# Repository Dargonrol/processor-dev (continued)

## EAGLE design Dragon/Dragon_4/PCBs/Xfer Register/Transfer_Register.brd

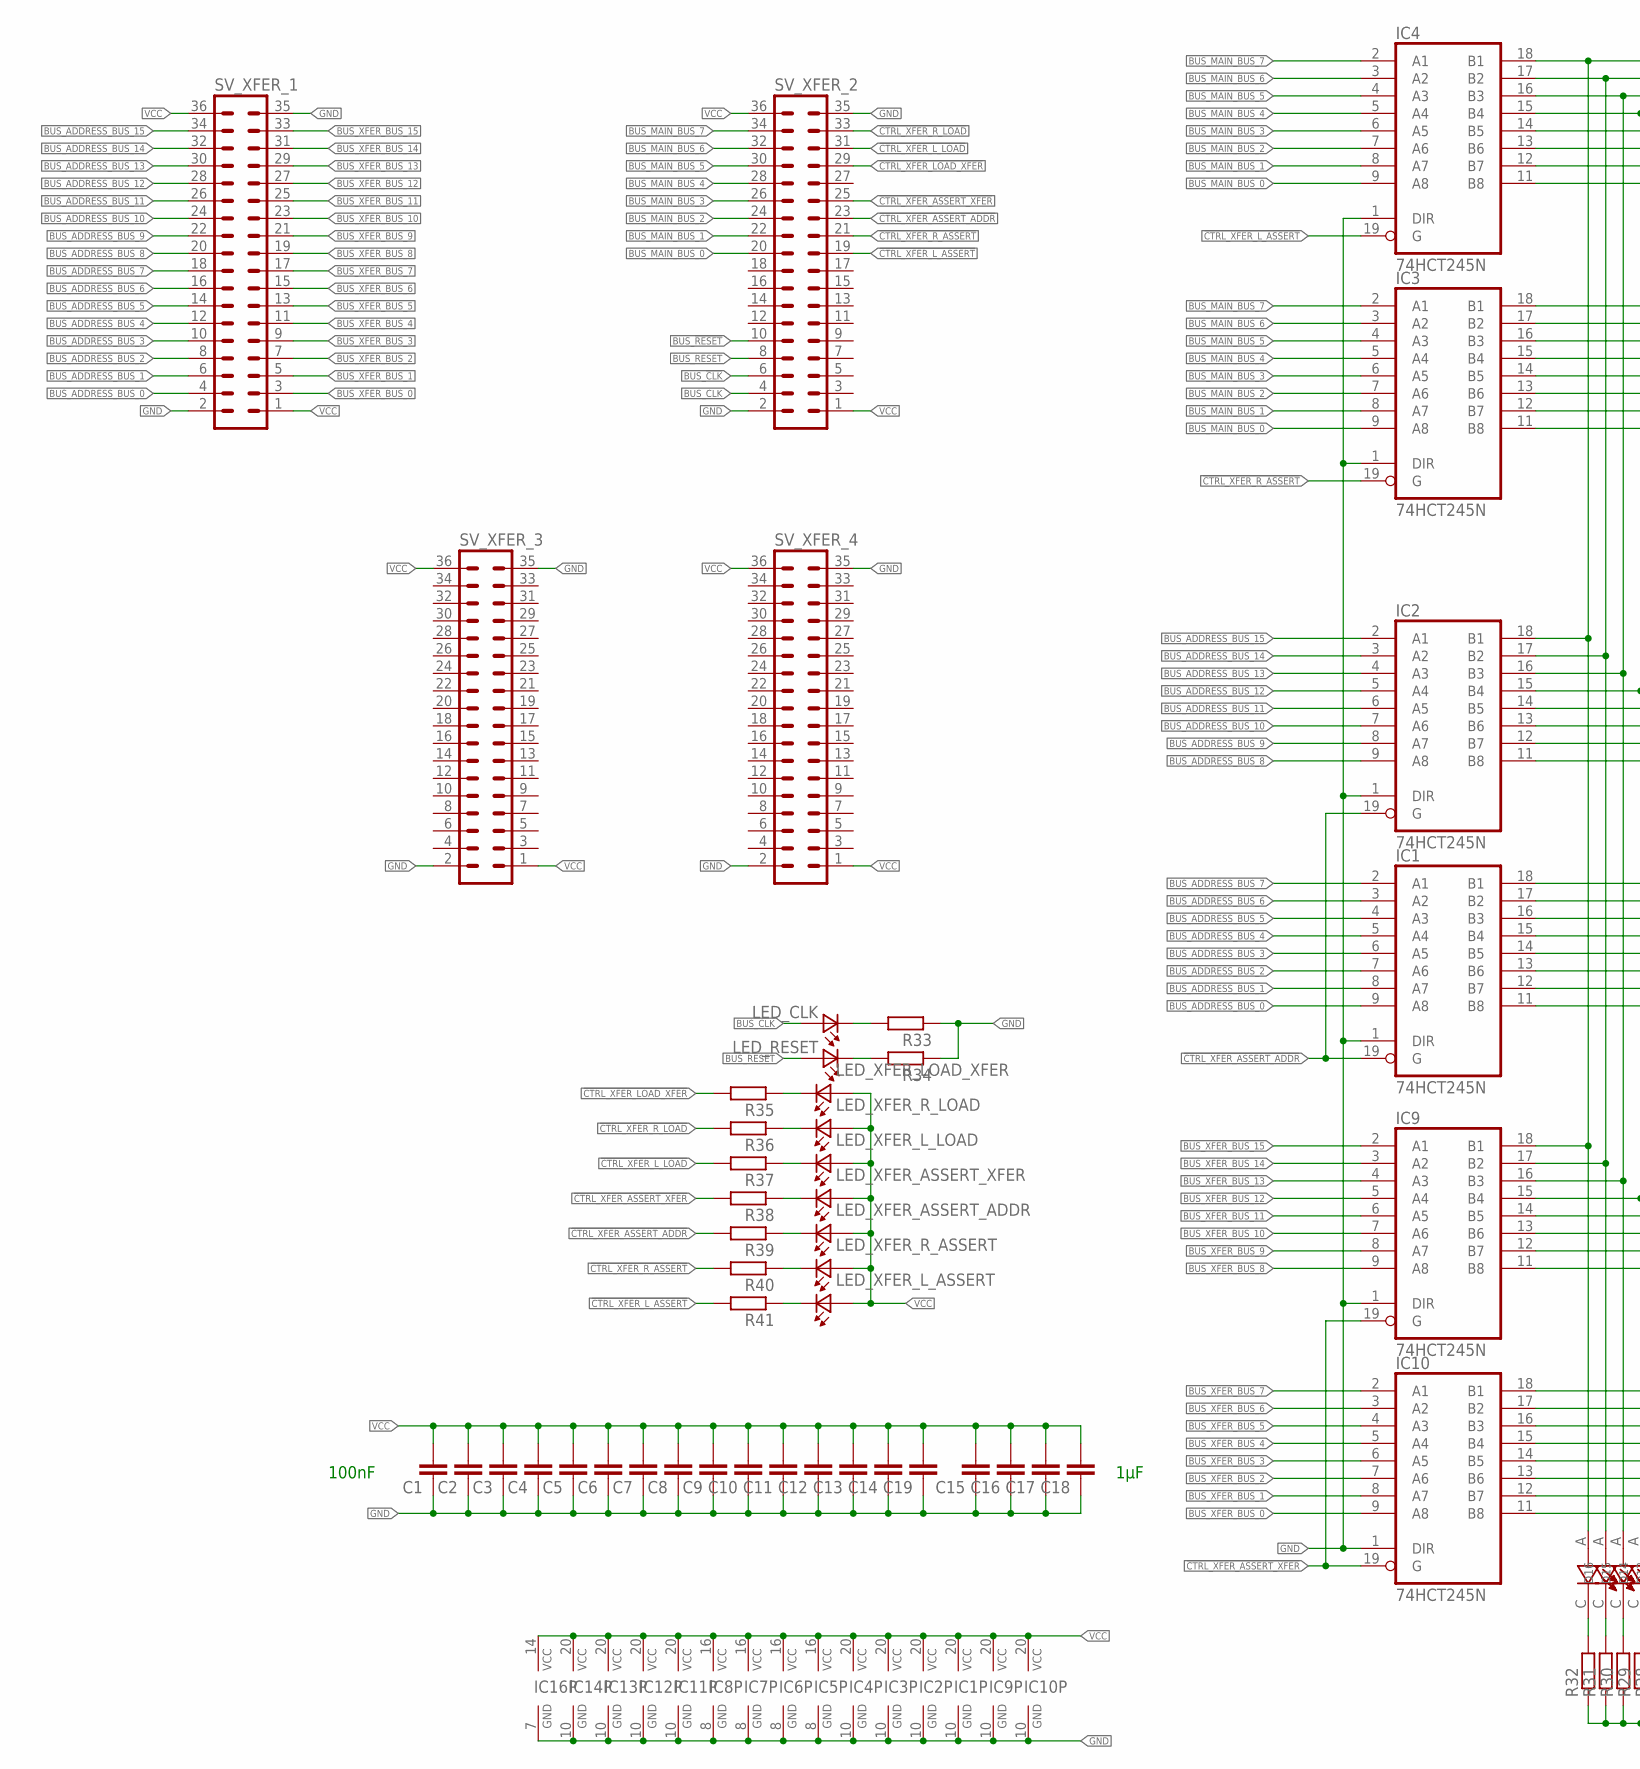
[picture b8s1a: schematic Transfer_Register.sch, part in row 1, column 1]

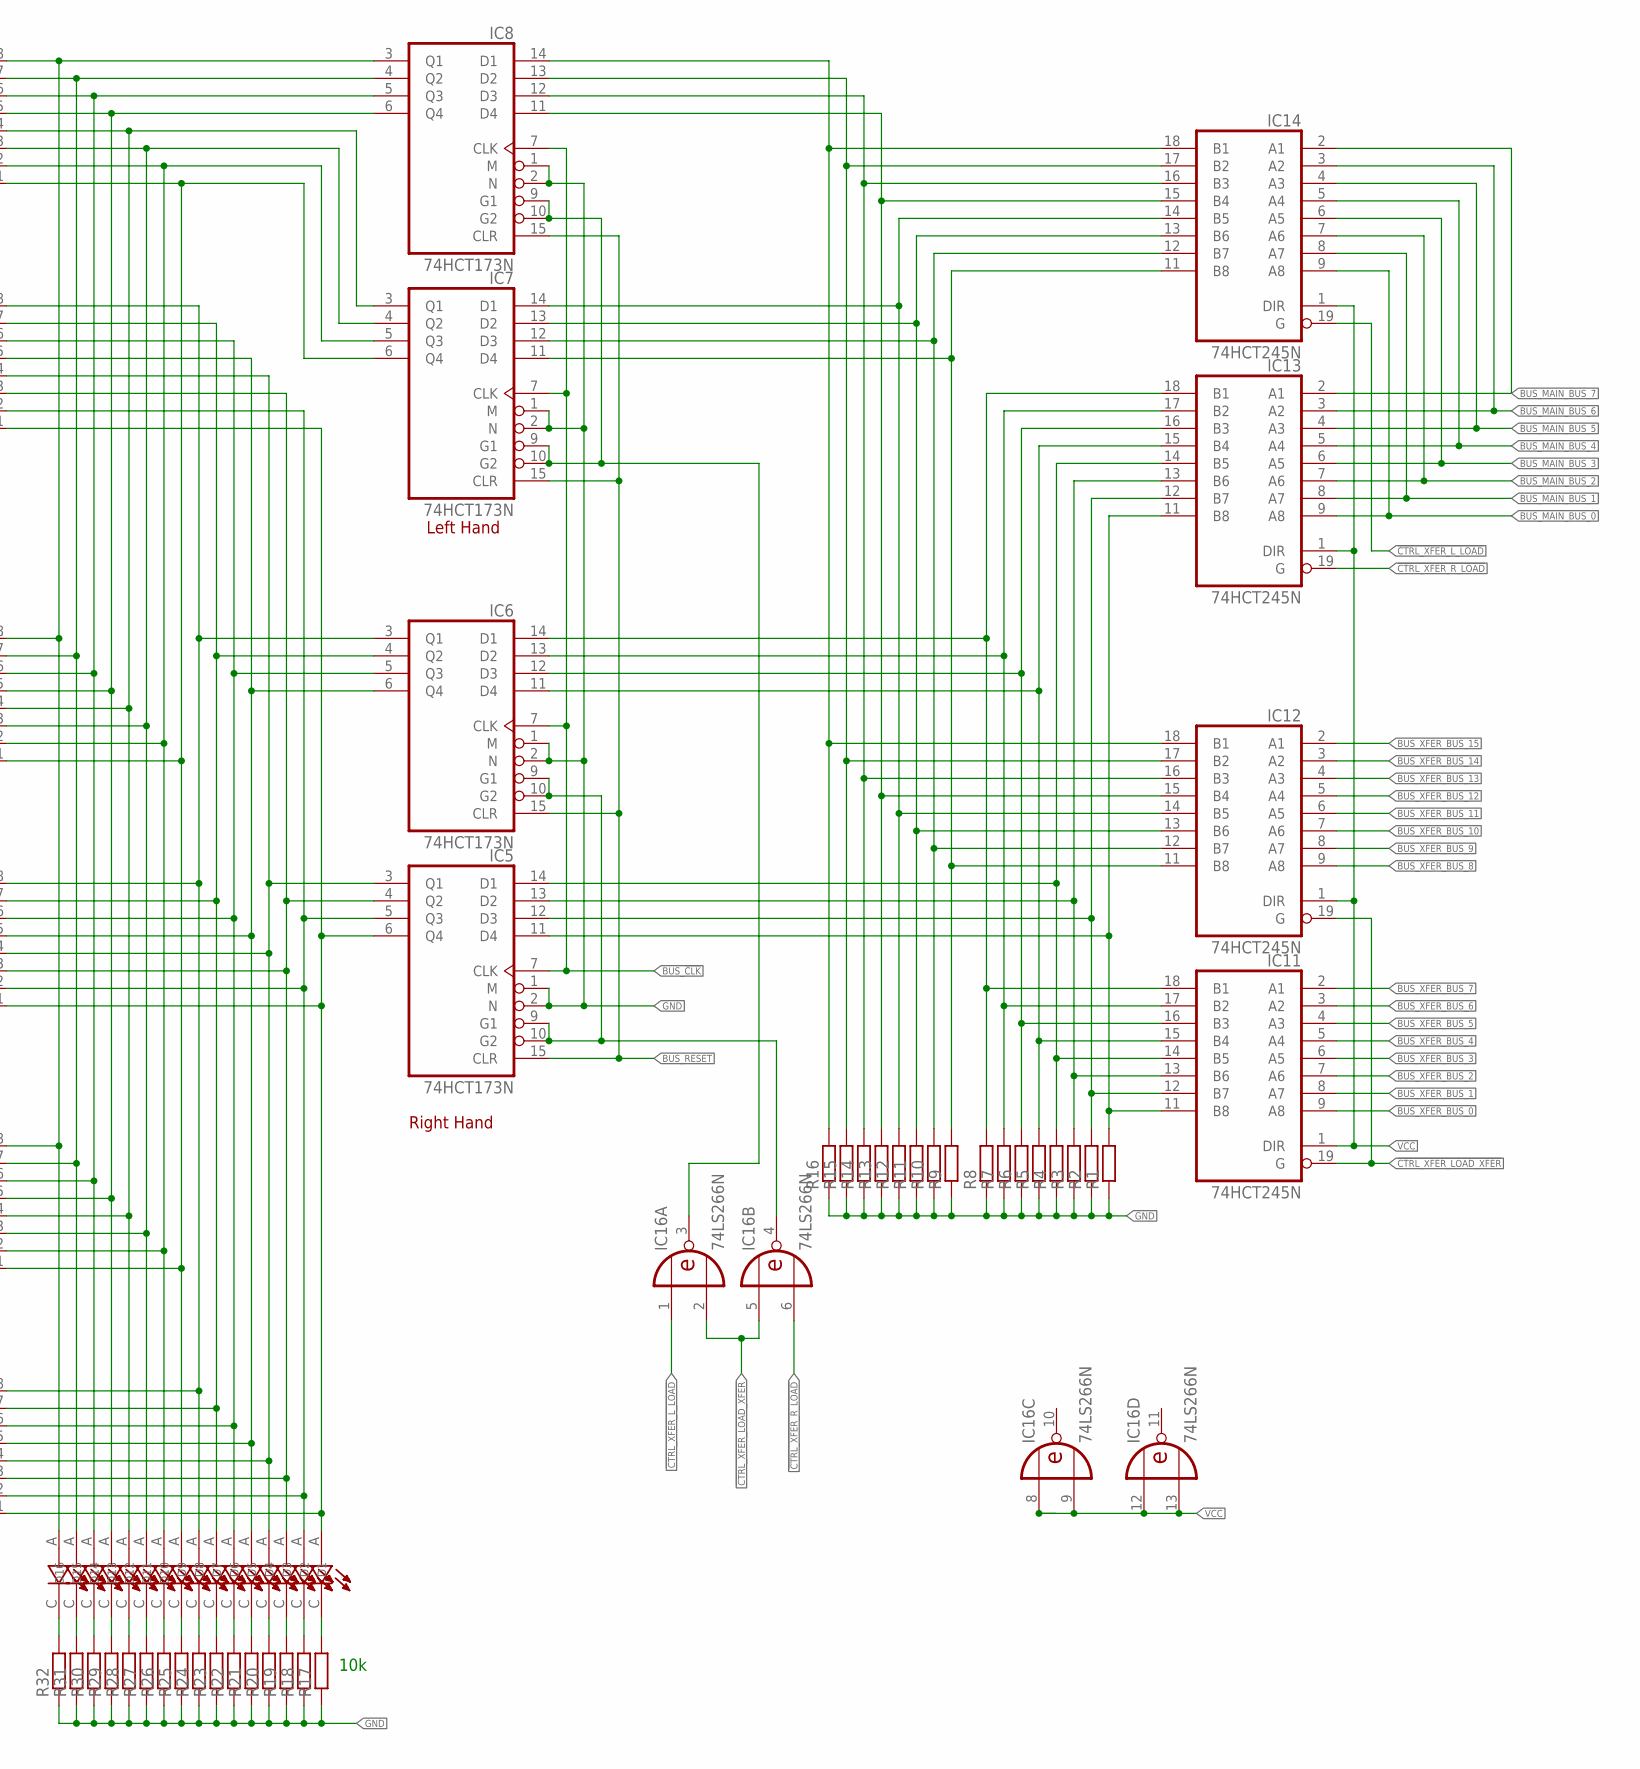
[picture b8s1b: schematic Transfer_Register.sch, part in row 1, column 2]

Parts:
C1, C2, C3, C4, C5, C6, C7, C8, C9, C10, C11, C12, C13, C14, C15, C16, C17, C18, C19: C-EUC0805; C0805
D1, D2, D3, D4, D5, D6, D7, D8, D9, D10, D11, D12, D13, D14, D15, D16: LTST-C193KRKT-5A; LEDC1608X45N
IC1, IC2, IC3, IC4, IC9, IC10, IC11, IC12, IC13, IC14: 74HCT245N; DIL20
IC5, IC6, IC7, IC8: 74HCT173N; DIL16
IC16: 74LS266N; DIL14
LED_CLK: LTST-C193TBKT-5A; 0603
LED_RESET: LTST-C193TBKT-5A; 0603
LED_XFER_ASSERT_ADDR: LTST-C193TBKT-5A; 0603
LED_XFER_ASSERT_XFER: LTST-C193TBKT-5A; 0603
LED_XFER_LOAD_XFER: LTST-C193TBKT-5A; 0603
LED_XFER_L_ASSERT: LTST-C193TBKT-5A; 0603
LED_XFER_L_LOAD: LTST-C193TBKT-5A; 0603
LED_XFER_R_ASSERT: LTST-C193TBKT-5A; 0603
LED_XFER_R_LOAD: LTST-C193TBKT-5A; 0603
R1, R2, R3, R4, R5, R6, R7, R8, R9, R10, R11, R12, R13, R14, R15, R16, R17, R18, R19, R20, R21, R22, R23, R24, R25, R26, R27, R28, R29, R30, R31, R32, R33, R34, R35, R36, R37, R38, R39, R40, R41: R-EU_R0805; R0805
SV_XFER_1, SV_XFER_2, SV_XFER_3, SV_XFER_4: MA18-2

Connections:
!CTRL_XFER_ASSERT_ADDR: IC1.19 (G), IC2.19 (G), R39.2, SV_XFER_2.23
!CTRL_XFER_ASSERT_XFER: IC9.19 (G), IC10.19 (G), R38.2, SV_XFER_2.25
!CTRL_XFER_LOAD_XFER: IC11.19 (G), IC12.19 (G), IC16.2 (I1), IC16.5 (I0), R35.2, SV_XFER_2.29
!CTRL_XFER_L_ASSERT: IC4.19 (G), R41.2, SV_XFER_2.19
!CTRL_XFER_L_LOAD: IC14.19 (G), IC16.1 (I0), R37.2, SV_XFER_2.31
!CTRL_XFER_R_ASSERT: IC3.19 (G), R40.2, SV_XFER_2.21
!CTRL_XFER_R_LOAD: IC13.19 (G), IC16.6 (I1), R36.2, SV_XFER_2.33
BUS_!CLK: IC5.7 (CLK), IC6.7 (CLK), IC7.7 (CLK), IC8.7 (CLK), SV_XFER_2.6
BUS_!RESET: SV_XFER_2.10
BUS_ADDRESS_BUS_0: IC1.9 (A8), SV_XFER_1.4
BUS_ADDRESS_BUS_1: IC1.8 (A7), SV_XFER_1.6
BUS_ADDRESS_BUS_2: IC1.7 (A6), SV_XFER_1.8
BUS_ADDRESS_BUS_3: IC1.6 (A5), SV_XFER_1.10
BUS_ADDRESS_BUS_4: IC1.5 (A4), SV_XFER_1.12
BUS_ADDRESS_BUS_5: IC1.4 (A3), SV_XFER_1.14
BUS_ADDRESS_BUS_6: IC1.3 (A2), SV_XFER_1.16
BUS_ADDRESS_BUS_7: IC1.2 (A1), SV_XFER_1.18
BUS_ADDRESS_BUS_8: IC2.9 (A8), SV_XFER_1.20
BUS_ADDRESS_BUS_9: IC2.8 (A7), SV_XFER_1.22
BUS_ADDRESS_BUS_10: IC2.7 (A6), SV_XFER_1.24
BUS_ADDRESS_BUS_11: IC2.6 (A5), SV_XFER_1.26
BUS_ADDRESS_BUS_12: IC2.5 (A4), SV_XFER_1.28
BUS_ADDRESS_BUS_13: IC2.4 (A3), SV_XFER_1.30
BUS_ADDRESS_BUS_14: IC2.3 (A2), SV_XFER_1.32
BUS_ADDRESS_BUS_15: IC2.2 (A1), SV_XFER_1.34
BUS_CLK: LED_CLK.2 (A2), SV_XFER_2.4
BUS_MAIN_BUS_0: IC3.9 (A8), IC4.9 (A8), IC13.9 (A8), IC14.9 (A8), SV_XFER_2.20
BUS_MAIN_BUS_1: IC3.8 (A7), IC4.8 (A7), IC13.8 (A7), IC14.8 (A7), SV_XFER_2.22
BUS_MAIN_BUS_2: IC3.7 (A6), IC4.7 (A6), IC13.7 (A6), IC14.7 (A6), SV_XFER_2.24
BUS_MAIN_BUS_3: IC3.6 (A5), IC4.6 (A5), IC13.6 (A5), IC14.6 (A5), SV_XFER_2.26
BUS_MAIN_BUS_4: IC3.5 (A4), IC4.5 (A4), IC13.5 (A4), IC14.5 (A4), SV_XFER_2.28
BUS_MAIN_BUS_5: IC3.4 (A3), IC4.4 (A3), IC13.4 (A3), IC14.4 (A3), SV_XFER_2.30
BUS_MAIN_BUS_6: IC3.3 (A2), IC4.3 (A2), IC13.3 (A2), IC14.3 (A2), SV_XFER_2.32
BUS_MAIN_BUS_7: IC3.2 (A1), IC4.2 (A1), IC13.2 (A1), IC14.2 (A1), SV_XFER_2.34
BUS_RESET: IC5.15 (CLR), IC6.15 (CLR), IC7.15 (CLR), IC8.15 (CLR), LED_RESET.2 (A2), SV_XFER_2.8
BUS_XFER_BUS_0: IC10.9 (A8), IC11.9 (A8), SV_XFER_1.3
BUS_XFER_BUS_1: IC10.8 (A7), IC11.8 (A7), SV_XFER_1.5
BUS_XFER_BUS_2: IC10.7 (A6), IC11.7 (A6), SV_XFER_1.7
BUS_XFER_BUS_3: IC10.6 (A5), IC11.6 (A5), SV_XFER_1.9
BUS_XFER_BUS_4: IC10.5 (A4), IC11.5 (A4), SV_XFER_1.11
BUS_XFER_BUS_5: IC10.4 (A3), IC11.4 (A3), SV_XFER_1.13
BUS_XFER_BUS_6: IC10.3 (A2), IC11.3 (A2), SV_XFER_1.15
BUS_XFER_BUS_7: IC10.2 (A1), IC11.2 (A1), SV_XFER_1.17
BUS_XFER_BUS_8: IC9.9 (A8), IC12.9 (A8), SV_XFER_1.19
BUS_XFER_BUS_9: IC9.8 (A7), IC12.8 (A7), SV_XFER_1.21
BUS_XFER_BUS_10: IC9.7 (A6), IC12.7 (A6), SV_XFER_1.23
BUS_XFER_BUS_11: IC9.6 (A5), IC12.6 (A5), SV_XFER_1.25
BUS_XFER_BUS_12: IC9.5 (A4), IC12.5 (A4), SV_XFER_1.27
BUS_XFER_BUS_13: IC9.4 (A3), IC12.4 (A3), SV_XFER_1.29
BUS_XFER_BUS_14: IC9.3 (A2), IC12.3 (A2), SV_XFER_1.31
BUS_XFER_BUS_15: IC9.2 (A1), IC12.2 (A1), SV_XFER_1.33
GND: C1.1, C2.1, C3.1, C4.1, C5.1, C6.1, C7.1, C8.1, C9.1, C10.1, C11.1, C12.1, C13.1, C14.1, C15.1, C16.1, C17.1, C18.1, C19.1, IC1.1 (DIR), IC1.10 (GND), IC2.1 (DIR), IC2.10 (GND), IC3.1 (DIR), IC3.10 (GND), IC4.1 (DIR), IC4.10 (GND), IC5.1 (M), IC5.2 (N), IC5.8 (GND), IC6.1 (M), IC6.2 (N), IC6.8 (GND), IC7.1 (M), IC7.2 (N), IC7.8 (GND), IC8.1 (M), IC8.2 (N), IC8.8 (GND), IC9.1 (DIR), IC9.10 (GND), IC10.1 (DIR), IC10.10 (GND), IC11.10 (GND), IC12.10 (GND), IC13.10 (GND), IC14.10 (GND), IC16.7 (GND), R1.1, R2.1, R3.1, R4.1, R5.1, R6.1, R7.1, R8.1, R9.1, R10.1, R11.1, R12.1, R13.1, R14.1, R15.1, R16.1, R17.1, R18.1, R19.1, R20.1, R21.1, R22.1, R23.1, R24.1, R25.1, R26.1, R27.1, R28.1, R29.1, R30.1, R31.1, R32.1, R33.1, R34.1, SV_XFER_1.2, SV_XFER_1.35, SV_XFER_2.2, SV_XFER_2.35, SV_XFER_3.2, SV_XFER_3.35, SV_XFER_4.2, SV_XFER_4.35
unnamed: LED_CLK.1 (K2), R33.2
unnamed: LED_RESET.1 (K2), R34.2
unnamed: LED_XFER_LOAD_XFER.1 (K2), R35.1
unnamed: LED_XFER_R_LOAD.1 (K2), R36.1
unnamed: LED_XFER_L_LOAD.1 (K2), R37.1
unnamed: LED_XFER_ASSERT_XFER.1 (K2), R38.1
unnamed: LED_XFER_ASSERT_ADDR.1 (K2), R39.1
unnamed: LED_XFER_R_ASSERT.1 (K2), R40.1
unnamed: LED_XFER_L_ASSERT.1 (K2), R41.1
unnamed: D16.A, IC2.18 (B1), IC4.18 (B1), IC8.3 (Q1), IC9.18 (B1)
unnamed: D15.A, IC2.17 (B2), IC4.17 (B2), IC8.4 (Q2), IC9.17 (B2)
unnamed: D14.A, IC2.16 (B3), IC4.16 (B3), IC8.5 (Q3), IC9.16 (B3)
unnamed: D13.A, IC2.15 (B4), IC4.15 (B4), IC8.6 (Q4), IC9.15 (B4)
unnamed: D12.A, IC2.14 (B5), IC4.14 (B5), IC7.3 (Q1), IC9.14 (B5)
unnamed: D11.A, IC2.13 (B6), IC4.13 (B6), IC7.4 (Q2), IC9.13 (B6)
unnamed: D10.A, IC2.12 (B7), IC4.12 (B7), IC7.5 (Q3), IC9.12 (B7)
unnamed: D9.A, IC2.11 (B8), IC4.11 (B8), IC7.6 (Q4), IC9.11 (B8)
unnamed: D8.A, IC1.18 (B1), IC3.18 (B1), IC6.3 (Q1), IC10.18 (B1)
unnamed: D7.A, IC1.17 (B2), IC3.17 (B2), IC6.4 (Q2), IC10.17 (B2)
unnamed: D6.A, IC1.16 (B3), IC3.16 (B3), IC6.5 (Q3), IC10.16 (B3)
unnamed: D5.A, IC1.15 (B4), IC3.15 (B4), IC6.6 (Q4), IC10.15 (B4)
unnamed: D4.A, IC1.14 (B5), IC3.14 (B5), IC5.3 (Q1), IC10.14 (B5)
unnamed: D3.A, IC1.13 (B6), IC3.13 (B6), IC5.4 (Q2), IC10.13 (B6)
unnamed: D2.A, IC1.12 (B7), IC3.12 (B7), IC5.5 (Q3), IC10.12 (B7)
unnamed: D1.A, IC1.11 (B8), IC3.11 (B8), IC5.6 (Q4), IC10.11 (B8)
unnamed: IC7.11 (D4), IC12.11 (B8), IC14.11 (B8), R9.2
unnamed: IC7.12 (D3), IC12.12 (B7), IC14.12 (B7), R10.2
unnamed: IC5.9 (G1), IC5.10 (G2), IC6.9 (G1), IC6.10 (G2), IC16.4 (O)
unnamed: IC7.13 (D2), IC12.13 (B6), IC14.13 (B6), R11.2
unnamed: IC7.9 (G1), IC7.10 (G2), IC8.9 (G1), IC8.10 (G2), IC16.3 (O)
unnamed: IC7.14 (D1), IC12.14 (B5), IC14.14 (B5), R12.2
unnamed: IC8.11 (D4), IC12.15 (B4), IC14.15 (B4), R13.2
unnamed: IC5.11 (D4), IC11.11 (B8), IC13.11 (B8), R1.2
unnamed: IC5.12 (D3), IC11.12 (B7), IC13.12 (B7), R2.2
unnamed: IC5.13 (D2), IC11.13 (B6), IC13.13 (B6), R3.2
unnamed: IC5.14 (D1), IC11.14 (B5), IC13.14 (B5), R4.2
unnamed: IC6.11 (D4), IC11.15 (B4), IC13.15 (B4), R5.2
unnamed: IC6.12 (D3), IC11.16 (B3), IC13.16 (B3), R6.2
unnamed: IC6.13 (D2), IC11.17 (B2), IC13.17 (B2), R7.2
unnamed: IC6.14 (D1), IC11.18 (B1), IC13.18 (B1), R8.2
unnamed: IC8.12 (D3), IC12.16 (B3), IC14.16 (B3), R14.2
unnamed: IC8.13 (D2), IC12.17 (B2), IC14.17 (B2), R15.2
unnamed: IC8.14 (D1), IC12.18 (B1), IC14.18 (B1), R16.2
unnamed: D1.C, R17.2
unnamed: D2.C, R18.2
unnamed: D3.C, R19.2
unnamed: D4.C, R20.2
unnamed: D5.C, R21.2
unnamed: D6.C, R22.2
unnamed: D7.C, R23.2
unnamed: D8.C, R24.2
unnamed: D9.C, R25.2
unnamed: D10.C, R26.2
unnamed: D11.C, R27.2
unnamed: D12.C, R28.2
unnamed: D13.C, R29.2
unnamed: D14.C, R30.2
unnamed: D15.C, R31.2
unnamed: D16.C, R32.2
VCC: C1.2, C2.2, C3.2, C4.2, C5.2, C6.2, C7.2, C8.2, C9.2, C10.2, C11.2, C12.2, C13.2, C14.2, C15.2, C16.2, C17.2, C18.2, C19.2, IC1.20 (VCC), IC2.20 (VCC), IC3.20 (VCC), IC4.20 (VCC), IC5.16 (VCC), IC6.16 (VCC), IC7.16 (VCC), IC8.16 (VCC), IC9.20 (VCC), IC10.20 (VCC), IC11.1 (DIR), IC11.20 (VCC), IC12.1 (DIR), IC12.20 (VCC), IC13.1 (DIR), IC13.20 (VCC), IC14.1 (DIR), IC14.20 (VCC), IC16.8 (I0), IC16.9 (I1), IC16.12 (I0), IC16.13 (I1), IC16.14 (VCC), LED_XFER_ASSERT_ADDR.2 (A2), LED_XFER_ASSERT_XFER.2 (A2), LED_XFER_LOAD_XFER.2 (A2), LED_XFER_L_ASSERT.2 (A2), LED_XFER_L_LOAD.2 (A2), LED_XFER_R_ASSERT.2 (A2), LED_XFER_R_LOAD.2 (A2), SV_XFER_1.1, SV_XFER_1.36, SV_XFER_2.1, SV_XFER_2.36, SV_XFER_3.1, SV_XFER_3.36, SV_XFER_4.1, SV_XFER_4.36

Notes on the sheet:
Right Hand
Left Hand
10k
100nF
1µF

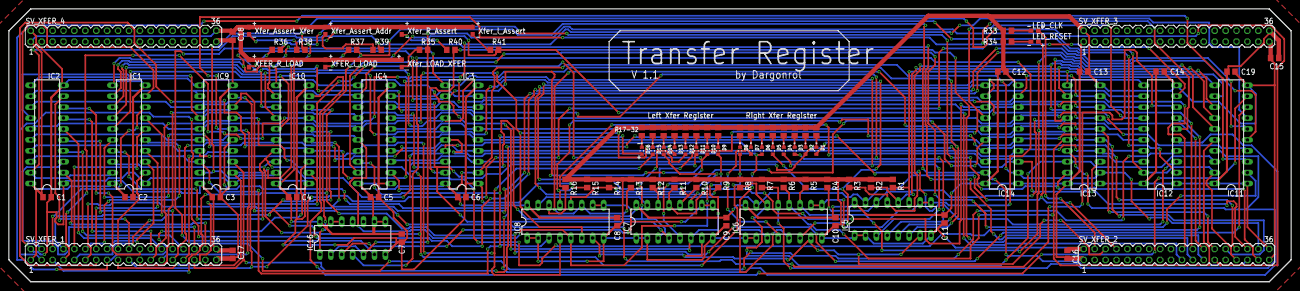
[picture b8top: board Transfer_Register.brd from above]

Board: 2 copper layers, 298.4 x 63.5 mm, 104 parts (0 on the bottom side), 111 nets.

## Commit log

2024-06-28 inital commit
2024-07-10 refactored Phönix-2 into Dragon-5
2024-09-28 Dragon 5 is now Phönix-1
2025-06-12 created Dragon-5 instruction-set
2025-06-14 improved Dragon 5 ISA
2025-06-14 added readme
2025-06-22 removed old naming convention.txt
2025-08-28 fixed newline issue in docs
    Clarify the behavior of *SBi* instruction with immediate values.
2025-08-28 added missing files
2025-08-28 began PseudoInst translation
2025-09-02 Major ISA redesign, added docs, added changelog
    - created changelog
    - redesigned "Jumps and Branches" in the ISA; renamed -> "Jumps"
    - *after* thinking a lot, RISC-V type branches are going to be omitted in the ISA. The only advantage would be taking up 1 instruction less when branching. Only supporting jumps would get rid of the 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
    - created flags documentation
    - continued pseudo-instruction-translation-table
    - removed pseudo-instruction-translation-table
2025-11-03 added new PP slides for SFZSLS in Dragon-4
2025-12-05 several improvements in docs and ISA, continued microarchitecture corrected Instruction Types documentation and added additional information continued Microarchitecture diagram (SVG) improved instruc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
2025-12-06 Continued microarchitecture, small fixes - continued microarchitecture diagram - fixed jumps explanation in ISA - after careful consideration, omitted the variable instruction length idea because it 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
2025-12-07 Continued Microarchitecture, removed several instructions - continued Microarchitecture - removed **JBIT** instruction. while it is totally possible to implement this instruction, it requires special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
2025-12-07 worked on simulation | finished register file
2025-12-08 Rethought RAM, began implementing cache in sim. - Reimplemented Register file in simulation after thinking how to implement the register file IRL I noticed that this is pretty much impossible because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
2026-02-11 refactored archive
2026-03-04 changed obsidian theme :)
2026-03-04 continued instruction cache
2026-03-05 added missing changelog
2026-03-06 continued instruction cache, rethought design - continued simulation - replanned caches
2026-03-06 finished implementing caches in logisim - finished instruction cache - finished data cache - thought about RAM implementation
2026-03-06 began main memory - added Cache invalidation instructions - refactored a bunch of stuff - began partlist - began main memory in logisim - finished memory card - began working on main memory controlle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
2026-06-17 continued working on memory controller
2026-06-20 worked on Address Controler + Mem Bus
